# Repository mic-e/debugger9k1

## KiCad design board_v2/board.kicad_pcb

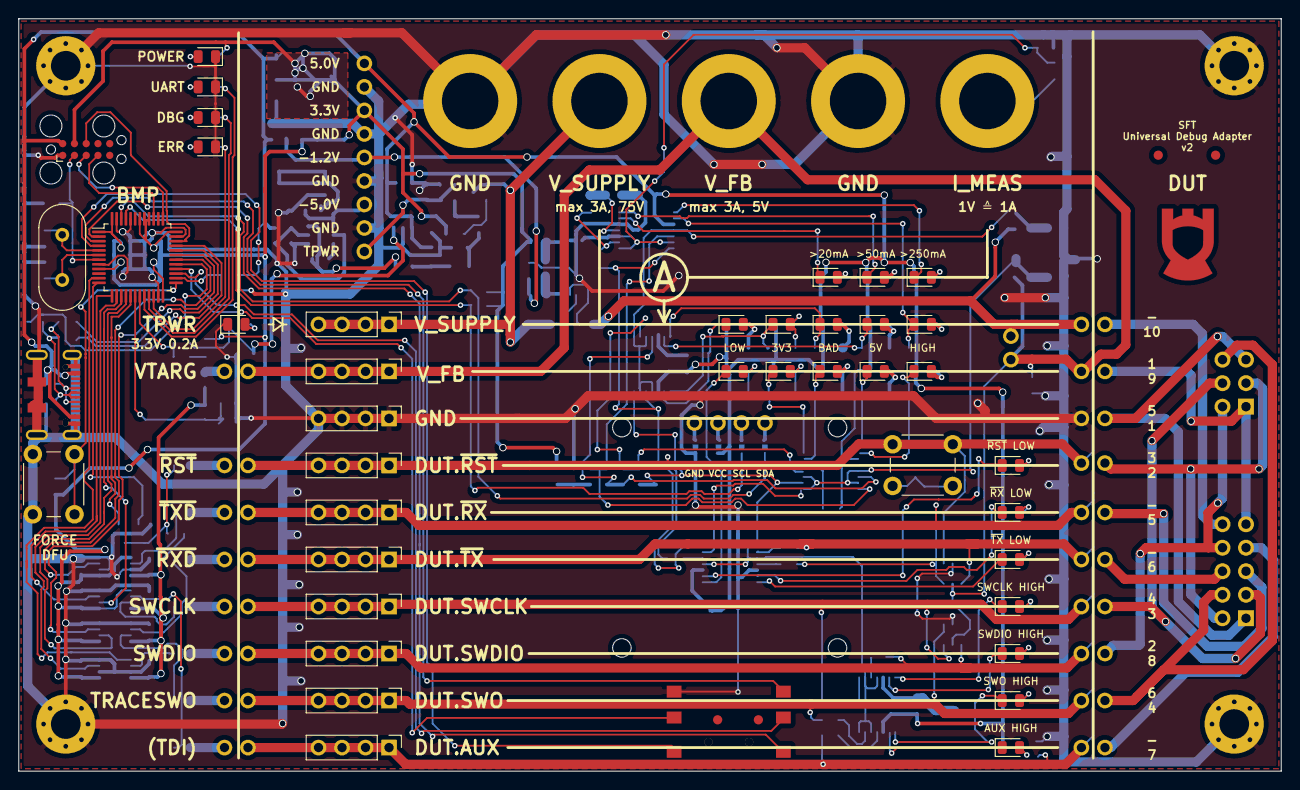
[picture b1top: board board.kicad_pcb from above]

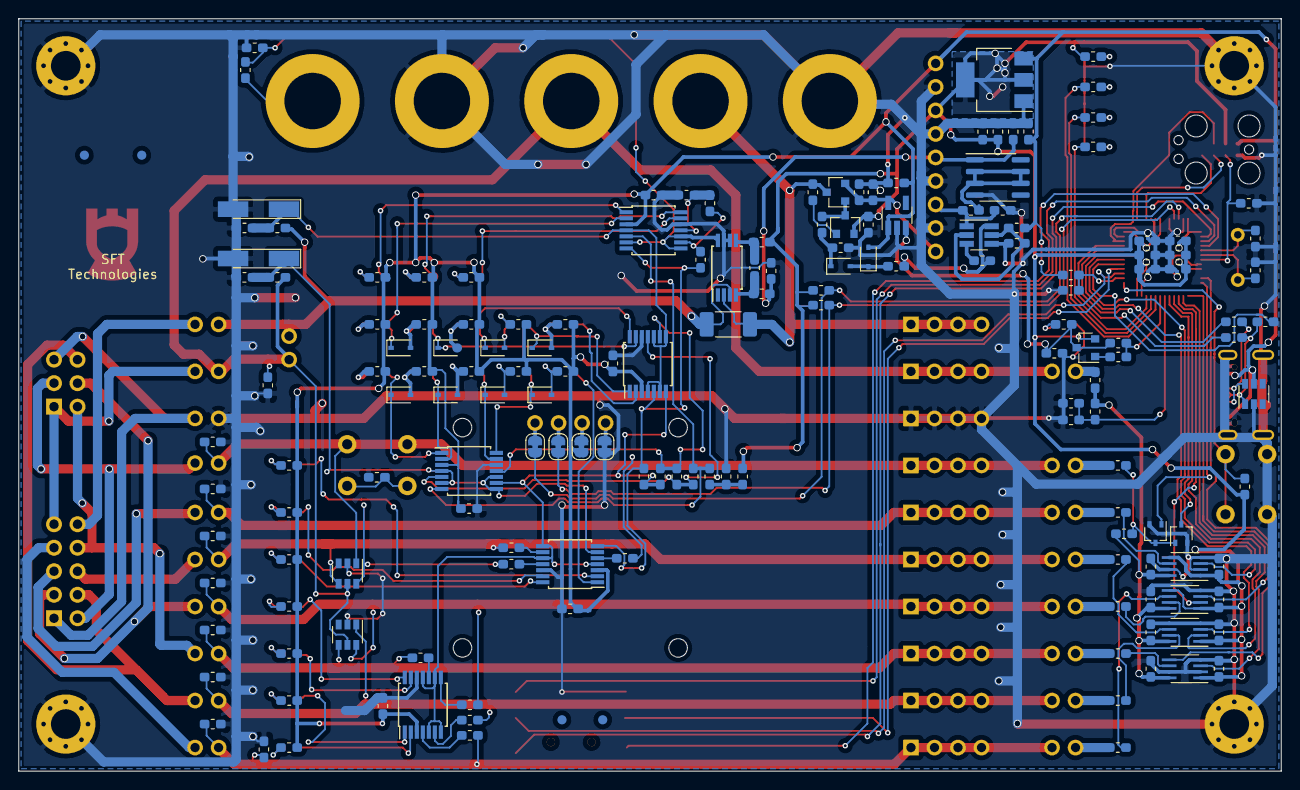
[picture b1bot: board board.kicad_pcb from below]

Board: 2 copper layers, 136.4 x 81.3 mm, 246 parts (167 on the bottom side), 157 nets.

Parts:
C1, C5, C7, C8, C9, C10, C11, C12, C13, C14, C15, C16, C17, C18, C19, C20, C21, C22, C23, C24, C25, C33, C34, C35, C36: 100nF; C_0603_1608Metric_Pad1.05x0.95mm_HandSolder
C2, C3: 18pF; C_0603_1608Metric_Pad1.05x0.95mm_HandSolder
C4, C6, C26, C29, C30, C31: 4.7uF; C_0603_1608Metric_Pad1.05x0.95mm_HandSolder
C27, C28: 10uF; C_0603_1608Metric_Pad1.05x0.95mm_HandSolder
C32: 1uF; C_0603_1608Metric_Pad1.05x0.95mm_HandSolder
D1, D6, D8, D15, D18, D20, D39: Green; LED_0805_2012Metric
D2, D3, D9, D10, D11, D14, D22, D23, D24, D25: Yellow; LED_0805_2012Metric
D4, D5, D7, D12, D13, D17, D19, D21: Red; LED_0805_2012Metric
D16, D26: 4.7V; D_MiniMELF_Handsoldering
D27, D29, D38: 24V ESD; R_0603_1608Metric_Pad1.05x0.95mm_HandSolder
D30, D31, D32, D33, D34, D35, D36, D37, D40, D41: 1N4148WS; D_SOD-323
FB1, FB2, FB3, FB4, FB5: 30Ω@100MHz; R_0603_1608Metric_Pad1.05x0.95mm_HandSolder
FID1, FID2, FID3, FID4, FID5, FID6, FID7, FID8: Fiducial; Fiducial_1mm_Mask2mm
H1, H2, H3, H4: MountingHole_Pad; MountingHole_3.2mm_M3_Pad_Via
J1: DX07S016JA; USB_C_JAE_DX07S0116JA1
J3, J4, J5, J6, J7, J8, J9, J10, J11, J12: Conn_01x04_Male; PinHeader_1x04_P2.54mm_Vertical
J13, J14, J15, J16, J17: Conn_01x01_Female; Connector_Banana_SKS_BIL20
J18: Conn_01x09; PinHeader_1x09_P2.54mm_Vertical
JP1, JP2, JP3, JP4, JP5, JP6, JP7, JP8, JP9, JP10, JP11, JP12, JP13, JP14, JP15, JP16, JP17, JP18, JP19: Jumper_NC_Small; Jumper_2.54mm
JP20, JP21, JP22, JP23: SolderJumper_2_Bridged; SolderJumper-2_P1.3mm_Bridged_RoundedPad1.0x1.5mm
LOGO1: Logo; LOGO_CU_070
Q1, Q2: N-Channel; SOT-323_SC-70
Q3: BC857B; SOT-23
Q4: N-Channel; SOT-23
Q5: BC848B; SOT-23
R1, R5, R7, R9, R50, R51, R61, R62, R72, R74, R76: 10k; R_0603_1608Metric_Pad1.05x0.95mm_HandSolder
R2, R11, R20, R21: 1k5; R_0603_1608Metric_Pad1.05x0.95mm_HandSolder
R3, R4: 22; R_0603_1608Metric_Pad1.05x0.95mm_HandSolder
R6, R8, R70, R71: 4k7; R_0603_1608Metric_Pad1.05x0.95mm_HandSolder
R10, R75: 15k; R_0603_1608Metric_Pad1.05x0.95mm_HandSolder
R12, R13, R14, R15, R16, R17, R18, R19: 100; R_0603_1608Metric_Pad1.05x0.95mm_HandSolder
R22: 50mOhm; R_2010_5025Metric_Pad1.52x2.65mm_HandSolder
R23, R36, R38, R43, R53, R55: 33k; R_0603_1608Metric_Pad1.05x0.95mm_HandSolder
R24: 30k; R_0603_1608Metric_Pad1.05x0.95mm_HandSolder
R25: 27k; R_0603_1608Metric_Pad1.05x0.95mm_HandSolder
R26: 18k; R_0603_1608Metric_Pad1.05x0.95mm_HandSolder
R27: 75k; R_0603_1608Metric_Pad1.05x0.95mm_HandSolder
R28: 12k; R_0603_1608Metric_Pad1.05x0.95mm_HandSolder
R29: 1k8; R_0603_1608Metric_Pad1.05x0.95mm_HandSolder
R30: 1k2; R_0603_1608Metric_Pad1.05x0.95mm_HandSolder
R31, R32, R33, R46, R47, R48, R49, R77, R78: 100k; R_0603_1608Metric_Pad1.05x0.95mm_HandSolder
R34, R81: 200; R_0603_1608Metric_Pad1.05x0.95mm_HandSolder
R35, R37, R39, R40, R41, R42, R44, R45, R52, R54, R56, R57, R58, R59, R60, R79: 3k3; R_0603_1608Metric_Pad1.05x0.95mm_HandSolder
R63, R64, R65, R66, R67, R68, R69: 1M; R_0603_1608Metric_Pad1.05x0.95mm_HandSolder
R73: 0; R_0603_1608Metric_Pad1.05x0.95mm_HandSolder
R80: 330; R_0603_1608Metric_Pad1.05x0.95mm_HandSolder
SW1, SW2: SW_Push; SW_PUSH_6mm_H4.3mm
SW3: K1-1504SA-03
U1: STM32F103CBTx; LQFP-48_7x7mm_P0.5mm
U2, U3, U5, U6: SN74LVC2T45DCT; TI-R-PDSO-G8
U4, U13, U14: USBLC6-4SC6; SOT-23-6
U7: INA240A1; TSSOP-8_4.4x3mm_P0.65mm
U8, U9, U10, U11, U12: TS339; TSSOP-14_4.4x5mm_P0.65mm
U15: NCP1117-3.3; SOT-223-3_TabPin2
U16: SGM3204; SOT-23-6_Handsoldering
U17: LM337L; SOIC-8_3.9x4.9mm_P1.27mm
U18: TLV70033; SOT-23-5_HandSoldering
X1: SFT_DEBUG_CONNECTOR-SELF; Tag-Connect_TC2050-IDC-FP_2x05_P1.27mm_Vertical
X2: SFT debugport; IDC-Header_2x05_P2.54mm_Vertical
X3: ARM debugport; IDC-Header_2x03_P2.54mm_Vertical
X4: Blue; OLED_128x64_096in
Y1: 8.000 MHz; Crystal_HC49-4H_Vertical

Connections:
+3V3: C4.2, C5.2, C6.2, C7.2, C8.2, C9.2, C12.2, C13.2, C14.2, C15.2, C28.2, C32.2, FB1.1, FB3.1, J18.3, Q3.2, Q5.2, R5.2, R10.1, R70.1, R71.1, R79.1, U1.1, U1.9, U1.24, U1.36, U1.40, U1.41, U1.42, U1.48, U2.1, U2.5, U3.1, U3.5, U5.1, U6.1, U15.2, X1.9
+5V: C21.1, C22.1, C23.1, C24.1, C25.1, C27.2, C33.1, D40.2, FB4.1, J1.A4/B9, J1.B4/A9, J18.1, JP22.2, R6.1, R35.1, R36.1, R37.1, R38.1, R39.1, R40.1, R41.1, R42.1, R43.1, R44.1, R45.1, R52.1, R53.1, R54.1, R55.1, R56.1, R57.1, R58.1, R59.1, R60.1, U4.5, U8.3, U9.3, U10.3, U11.3, U12.3, U15.3, U18.1, X1.10
-1V2: C31.2, FB2.2, J18.5, R80.1, U17.1
-5V: C30.2, FB5.1, J18.7, U16.1
/BlackMagicProbe/BMP.RXD: J4.1, J4.2, J4.3, J4.4, JP9.1, JP13.1, R31.2, R65.1, U13.4
/BlackMagicProbe/BMP.SWCLK: J6.1, J6.2, J6.3, J6.4, JP6.1, JP16.1, R47.2, R66.1, U14.6
/BlackMagicProbe/BMP.SWDIO: J8.1, J8.2, J8.3, J8.4, JP7.1, JP17.1, R48.2, R67.1, U14.4
/BlackMagicProbe/BMP.TDI: D27.1, J12.1, J12.2, J12.3, J12.4, JP4.1, JP19.1, R49.2, R69.1
/BlackMagicProbe/BMP.TRACESWO: J10.1, J10.2, J10.3, J10.4, JP5.1, JP18.1, R46.2, R68.1, U14.1
/BlackMagicProbe/BMP.TXD: J11.1, J11.2, J11.3, J11.4, JP8.1, JP14.1, R32.2, R64.1, U13.6
/BlackMagicProbe/BMP.VTARG: D29.1, J7.1, J7.2, J7.3, J7.4, J14.1, JP1.2, JP2.1, JP12.1, R61.1, U13.5, U14.5
/BlackMagicProbe/BMP.~RST: J9.1, J9.2, J9.3, J9.4, JP3.1, JP15.1, R33.2, R63.1, SW1.1, U13.1
/BlackMagicProbe/BMP.~TPWR_EN: R72.1, R73.1, U1.19
/BlackMagicProbe/FORCE_DFU: R5.1, SW2.1, U1.25
/BlackMagicProbe/INTERFACE_NATIVE_RST: Q1.1, U1.12
/BlackMagicProbe/INTERFACE_NATIVE_RST_SENSE: Q2.3, U1.17
/BlackMagicProbe/INTERFACE_NATIVE_RXD: U1.31, U6.3
/BlackMagicProbe/INTERFACE_NATIVE_SWDIO_DIR: U1.11, U5.5
/BlackMagicProbe/INTERFACE_NATIVE_TCK_SWCLK: U1.15, U3.2
/BlackMagicProbe/INTERFACE_NATIVE_TDI: U1.13, U3.3
/BlackMagicProbe/INTERFACE_NATIVE_TDO_TRACESWO: U1.16, U6.2
/BlackMagicProbe/INTERFACE_NATIVE_TMS_SWDIO: U1.14, U5.3
/BlackMagicProbe/INTERFACE_NATIVE_TXD: U1.30, U2.3
/BlackMagicProbe/INTERFACE_TARGET_RXD: R19.2, U6.6
/BlackMagicProbe/INTERFACE_TARGET_TCK_SWCLK: R16.2, U3.7
/BlackMagicProbe/INTERFACE_TARGET_TDI: R14.2, U3.6
/BlackMagicProbe/INTERFACE_TARGET_TDO_TRACESWO: R15.2, U6.7
/BlackMagicProbe/INTERFACE_TARGET_TMS_SWDIO: R17.2, U5.6
/BlackMagicProbe/INTERFACE_TARGET_TXD: R18.2, U2.6
/BlackMagicProbe/INTERFACE_TARGET_~RST: Q1.3, Q2.1, R1.2, R13.2
/BlackMagicProbe/LED0: R11.1, U1.20
/BlackMagicProbe/LED1: R20.1, U1.21
/BlackMagicProbe/LED2: R21.1, U1.22
/BlackMagicProbe/SELF_SWCLK: U1.37, X1.3
/BlackMagicProbe/SELF_SWDIO: U1.34, X1.8
/BlackMagicProbe/SELF_TRACESWO: U1.39, X1.4
/BlackMagicProbe/SELF_~RST: C1.1, U1.7, X1.2
/BlackMagicProbe/UI.SCL: JP20.1, R70.2, U1.45
/BlackMagicProbe/UI.SDA: JP21.1, R71.2, U1.46
/BlackMagicProbe/UI.~BUTTON_DOWN: SW3.4, U1.3
/BlackMagicProbe/UI.~BUTTON_LEFT: SW3.5, U1.27
/BlackMagicProbe/UI.~BUTTON_PRESS: SW3.3, U1.4
/BlackMagicProbe/UI.~BUTTON_RIGHT: SW3.2, U1.28
/BlackMagicProbe/UI.~BUTTON_UP: SW3.6, U1.2
/BlackMagicProbe/USB+: R4.2, U1.33
/BlackMagicProbe/USB-: R3.2, U1.32
/BlackMagicProbe/USB_1K5_PULLUP_CTRL: R2.2, U1.29
/BlackMagicProbe/USB_D+: J1.A6, J1.B6, R2.1, R4.1, U4.1
/BlackMagicProbe/USB_D-: J1.A7, J1.B7, R3.1, U4.6
/BlackMagicProbe/VBUS_MEAS: R6.2, R7.1, U1.26
/BlackMagicProbe/VTARG: C10.1, C11.1, C16.1, C17.1, R1.1, R8.1, R12.2, U2.8, U3.8, U5.8, U6.8
/BlackMagicProbe/VTARG_MEAS: C18.2, R8.2, R9.1, U1.18
/OutputInterface/3V3_FILTERED: C19.1, FB1.2, U7.5
/OutputInterface/-1V2_FILTERED: C19.2, FB2.1, U7.4
/OutputInterface/DUT.V_SUPPLY: J5.1, J5.2, J5.3, J5.4, J13.1, Q4.3, R22.2, R78.2, U7.2
/OutputInterface/I_SUPPLY: D38.1, R81.2, U7.8, U10.6, U10.8, U10.10
/OutputInterface/VREF_20mV: R29.2, R30.1, U10.11
/OutputInterface/VREF_50mV: R28.2, R29.1, U10.9
/OutputInterface/VREF_250mV: R27.2, R28.1, U8.5, U9.7, U10.7
/OutputInterface/VREF_1500mV: R26.2, R27.1, U8.7, U9.4, U9.8, U9.10, U11.9, U12.5, U12.7, U12.9, U12.11
/OutputInterface/VREF_1800mV: R25.2, R26.1, U8.9, U11.11
/OutputInterface/VREF_2250mV: R24.2, R25.1, U8.11, U11.5
/OutputInterface/VREF_2750mV: R23.1, R24.1, U10.5, U11.7
/OutputInterface/VREF_3300mV: C20.1, FB3.2, R23.2
/OutputInterface/V_FB_DIVIDED: D26.1, R61.2, R62.1, U9.6, U11.4, U11.6, U11.8, U11.10
/OutputInterface/V_SUPPLY: JP1.1, JP11.1, R22.1, R50.1, U7.3
/OutputInterface/V_SUPPLY_DIVIDED: D16.1, R50.2, R51.1, U8.4, U8.6, U8.8, U8.10, U10.4
/Power/3V3_TPWR: C35.1, J18.9, Q4.2, R76.1, U18.5
/Power/CFLY+: C29.2, C34.1, U16.6
GND: C1.2, C2.2, C3.2, C4.1, C5.1, C6.1, C7.1, C8.1, C9.1, C10.2, C11.2, C12.1, C13.1, C14.1, C15.1, C16.2, C17.2, C18.1, C20.2, C21.2, C22.2, C23.2, C24.2, C25.2, C26.1, C27.1, C28.1, C30.1, C31.1, C32.1, C33.2, C35.2, C36.1, D1.1, D2.1, D3.1, D4.1, D16.2, D26.2, D27.2, D29.2, D38.2, D39.1, H1.1, H2.1, H3.1, H4.1, J1.A1/B12, J1.B1/A12, J1.S1, J3.1, J3.2, J3.3, J3.4, J16.1, J17.1, J18.2, J18.4, J18.6, J18.8, JP10.1, JP23.2, Q1.2, Q2.2, R7.2, R9.2, R30.2, R34.1, R51.2, R62.2, R63.2, R64.2, R65.2, R66.2, R67.2, R68.2, R69.2, R74.2, R76.2, R79.2, R80.2, SW2.2, SW3.1, U1.8, U1.23, U1.35, U1.44, U1.47, U2.2, U2.4, U2.7, U3.4, U4.2, U5.2, U5.4, U5.7, U6.4, U6.5, U7.6, U7.7, U8.12, U9.12, U10.12, U11.12, U12.12, U13.2, U14.2, U15.1, U16.4, U17.4, U18.2, X1.1
unnamed: C2.1, U1.5, Y1.1
unnamed: C3.1, U1.6, Y1.2
unnamed: C26.2, FB4.2, U16.2, U16.5
unnamed: C29.1, U16.3
unnamed: C34.2, D40.1, D41.2
unnamed: C36.2, D41.1, R77.2
unnamed: D1.2, R10.2
unnamed: D2.2, R11.2
unnamed: D3.2, R20.2
unnamed: D4.2, R21.2
unnamed: D5.1, U8.2
unnamed: D9.2, R39.2
unnamed: D10.1, U9.14
unnamed: D10.2, R40.2
unnamed: D11.1, U9.13
unnamed: D11.2, R41.2
unnamed: D12.1, U9.2
unnamed: D12.2, R42.2
unnamed: D13.1, U10.1
unnamed: D13.2, R43.2
unnamed: D14.1, U10.14
unnamed: D14.2, R44.2
unnamed: D15.1, U10.13
unnamed: D15.2, R45.2
unnamed: D17.1, U9.1
unnamed: D17.2, D34.2, R52.2
unnamed: D18.1, D34.1, U11.14
unnamed: D18.2, D35.2, R53.2
unnamed: D19.1, D35.1, U11.13
unnamed: D19.2, D36.2, R54.2
unnamed: D20.1, D36.1, U11.2
unnamed: D20.2, D37.2, R55.2
unnamed: D21.1, D37.1, U11.1
unnamed: D21.2, R56.2
unnamed: D22.1, U12.1
unnamed: D22.2, R57.2
unnamed: D23.1, U12.14
unnamed: D23.2, R58.2
unnamed: D24.1, U12.13
unnamed: D24.2, R59.2
unnamed: D25.1, U12.2
unnamed: D25.2, R60.2
unnamed: D6.1, D30.1, U8.1
unnamed: D5.2, D30.2, R35.2
unnamed: D7.1, D31.1, U8.14
unnamed: D6.2, D31.2, R36.2
unnamed: D8.1, D32.1, U8.13
unnamed: D7.2, D32.2, R37.2
unnamed: D9.1, D33.1, U10.2
unnamed: D8.2, D33.2, R38.2
unnamed: D39.2, R75.2
unnamed: FB5.2, U17.2, U17.3, U17.6, U17.7
unnamed: J15.1, R81.1
unnamed: JP2.2, R12.1
unnamed: JP3.2, R13.1
unnamed: JP4.2, R14.1
unnamed: JP5.2, R15.1
unnamed: JP6.2, R16.1
unnamed: JP7.2, R17.1
unnamed: JP8.2, R18.1
unnamed: JP9.2, R19.1
unnamed: JP10.2, X2.1, X3.5
unnamed: JP11.2, X2.10
unnamed: JP12.2, X2.9, X3.1
unnamed: JP13.2, X2.6
unnamed: JP14.2, X2.5
unnamed: JP15.2, X2.2, X3.3
unnamed: JP16.2, X2.3, X3.4
unnamed: JP17.2, X2.8, X3.2
unnamed: JP18.2, X2.4, X3.6
unnamed: JP19.2, X2.7
unnamed: JP20.2, X4.3
unnamed: JP21.2, X4.4
unnamed: JP22.1, X4.2
unnamed: JP23.1, X4.1
unnamed: Q3.1, R72.2
unnamed: Q3.3, R73.2, R74.1, R75.1, U18.3
unnamed: Q4.1, Q5.3, R77.1
unnamed: Q5.1, R78.1
unnamed: R31.1, U9.9
unnamed: R32.1, U9.11
unnamed: R33.1, U9.5
unnamed: R34.2, SW1.2
unnamed: R46.1, U12.6
unnamed: R47.1, U12.8
unnamed: R48.1, U12.10
unnamed: R49.1, U12.4

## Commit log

2021-11-27 Release board v2
2022-05-30 Add issues and improvements for boardv2
2022-05-30 Weird changes to boards after they had been released and ordered
    This will not be merged to master but who knows
2022-05-30 Add history to boardv2
2022-05-30 Port sch and brd to kicad6
2022-05-30 Clean up kicad5 files in board_v2
2022-07-02 Update board v2 evaluation
